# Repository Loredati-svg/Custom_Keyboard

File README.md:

# RP2040 Macropad – 9 Keys & 2 Rotary Encoders

A custom 9-key macropad with two rotary encoders and per-key RGB lighting, designed from scratch in **KiCad 10** around a bare **RP2040** microcontroller.

---
## Libraries

This project uses the shared KiCad libraries from L2-Hardware.

1. Clone the library repository **in the same parent folder as your project folders**, so that it sits next to them:

```bash
   git clone https://github.com/L2-Hardware/Kicad_Libs
```

   Expected folder structure:

```
   Kicad/
   ├── Kicad_Libs/
   ├── Project1/
   ├── Project2/
   └── etc...
```

2. Inside the project folder, run the `bring_libs.bat` script to import the libraries into the project.
---
## Features

- **9 mechanical keys** in a 3×3 grid (Cherry MX compatible, PCB-mount, standard 19.05 mm pitch)
- **2 rotary encoders** with push button (Bourns PEC12R, 12 detents) – e.g. volume, scrolling, media control
- **Per-key RGB lighting** with 9 addressable SK6812MINI-E LEDs (reverse-mount, shining through the switch)
- **USB-C** connector (USB 2.0 Full Speed)
- **Bare RP2040** design (no module): QSPI flash, crystal and power supply on board
- **4-layer PCB**, all SMD components on the bottom side, only switches and encoders on top
- Designed for **QMK / VIA** firmware

---

## Block Diagram

```
USB-C ──► Polyfuse ──► VBUS (5 V) ──┬──► AP2112K-3.3 ──► +3V3 ──► RP2040, Flash, pull-ups
  │                                 │
  │                                 └──► SN74LV1T34 (3.3 V → 5 V) ──► SK6812MINI-E ×9 (daisy chain)
  │
  └── D+/D− ──► USBLC6-2SC6 (ESD) ──► 27 Ω ──► RP2040 USB
                                               │
                         W25Q32 QSPI Flash ◄───┤
                         12 MHz Crystal    ◄───┤
                         9 Keys            ◄───┤ GPIO0–8
                         2 Encoders        ◄───┤ GPIO9–14
                         LED data          ◄───┘ GPIO15
```

---

## Hardware

| Block | Part | Notes |
|---|---|---|
| MCU | **RP2040** (QFN-56) | Dual Cortex-M0+, internal 1.1 V core regulator |
| Flash | **W25Q32JV** (4 MB, QSPI) | Stores the firmware |
| Clock | **ABM8-272-T3** 12 MHz | 15 pF load caps, 1 kΩ series resistor on XOUT (per RP2040 hardware design guide) |
| LDO | **AP2112K-3.3** | 600 mA, VBUS → 3.3 V |
| USB | USB-C 16-pin receptacle | 5.1 kΩ pull-downs on CC1/CC2 (device/UFP) |
| ESD | **USBLC6-2SC6** | Flow-through layout on D+/D− |
| Protection | Resettable polyfuse | On VBUS input |
| Keys | Cherry MX compatible switches | Direct GPIO connection, no matrix / no diodes |
| Encoders | **Bourns PEC12R-4120F-S0012** | 12 pulses / 12 detents, push switch |
| LEDs | **SK6812MINI-E** ×9 | Reverse-mount, powered from VBUS |
| Level shifter | **SN74LV1T34** | Translates the 3.3 V LED data line to 5 V |

---

## Design Notes

**Direct-wired keys.** With only 9 keys and 2 encoders the RP2040 has plenty of GPIOs, so every key is wired directly to its own GPIO with the internal pull-up enabled. No key matrix and no diodes are needed, and there is no ghosting by design.

**Encoder filtering.** Each encoder channel (A/B) uses a 10 kΩ external pull-up plus an RC low-pass filter (10 kΩ / 10 nF, τ ≈ 0.1 ms) to suppress contact bounce in hardware, while still allowing fast rotation.

**LED data level shifting.** The SK6812 LEDs are supplied from 5 V, so their minimum input-high threshold is ≈ 0.7 × VDD = 3.5 V, above the RP2040's 3.3 V output. A single-gate SN74LV1T34 buffer powered from VBUS shifts the data line to 5 V. A 33 Ω series resistor dampens ringing, and a 10 kΩ pull-down keeps the data line low while the MCU is booting, so the LEDs do not flash randomly at power-up.

**LED power.** Each LED has its own 100 nF decoupling capacitor, plus a 10 µF bulk capacitor on VBUS. LED brightness should be capped in firmware to stay within the 500 mA USB 2.0 budget.

**USB.** The RP2040 runs USB 2.0 Full Speed (12 Mbps). D+/D− are routed as a differential pair over an unbroken ground plane, with the ESD protection in flow-through configuration and the 27 Ω series resistors placed close to the MCU.

**Boot mode.** A BOOT push-button pulls QSPI_SS low through a 1 kΩ resistor. Holding it while plugging in USB starts the RP2040 USB mass-storage bootloader (`RPI-RP2`). No reset button is needed: unplugging and replugging the cable does the same job. SWD (SWCLK/SWDIO) is exposed on test points for debugging.

---

## PCB

- **4 layers**, 1.6 mm
  - `F.Cu` – key / encoder signals
  - `POWER` – power plane (+3V3 / VBUS), some low-speed routing
  - `GND` – solid ground plane, reference for USB and bottom-side signals
  - `B.Cu` – all SMD components, USB pair
- **Single-sided SMD assembly** (bottom) to reduce assembly cost. Switches and encoders are through-hole and hand-soldered on top.
- Board cut-outs under each switch for the reverse-mount LEDs
- 4× **M3 mounting holes** for standoffs / case

---

## Pinout

| Function | GPIO |
|---|---|
| Keys SW2–SW10 | GP0 – GP8 |
| Encoder VR2 – A / B / Push | GP9 / GP10 / GP11 |
| Encoder VR1 – A / B / Push | GP12 / GP13 / GP14 |
| RGB LED data (9 LEDs) | GP15 |
| SWD | SWCLK / SWDIO (test points) |

---

## Flashing

1. Hold the **BOOT** button.
2. Plug in the USB-C cable.
3. Release the button. A drive called `RPI-RP2` appears.
4. Drag and drop the `.uf2` firmware file onto it. The board reboots automatically.

After the first flash, the bootloader can also be entered from a key mapped to `QK_BOOT` in QMK.

---

## Firmware

Planned: **QMK** with **VIA/Vial** support
- Encoders mapped with `ENCODER_MAP` (e.g. volume up/down + mute, scroll, media keys)
- `RGB_MATRIX` with the WS2812 PIO driver on GP15

---

## Repository Structure

```
Custom-Keyboard/
├── Kicad_Project/   # KiCad schematic, PCB and project files
├── Lib/             # Custom symbols, footprints and 3D models
└── 3D/              # 3D models / renders
```

---

## Project Status

- [x] Schematic
- [x] PCB layout (4-layer)
- [x] DRC / ERC clean
- [ ] Manufacturing
- [ ] Bring-up and testing
- [ ] QMK firmware

---

## Author

**Lorenzo Dati** – Analog IC Designer

<!-- Choose a license, e.g. CERN-OHL-S-2.0 for hardware -->

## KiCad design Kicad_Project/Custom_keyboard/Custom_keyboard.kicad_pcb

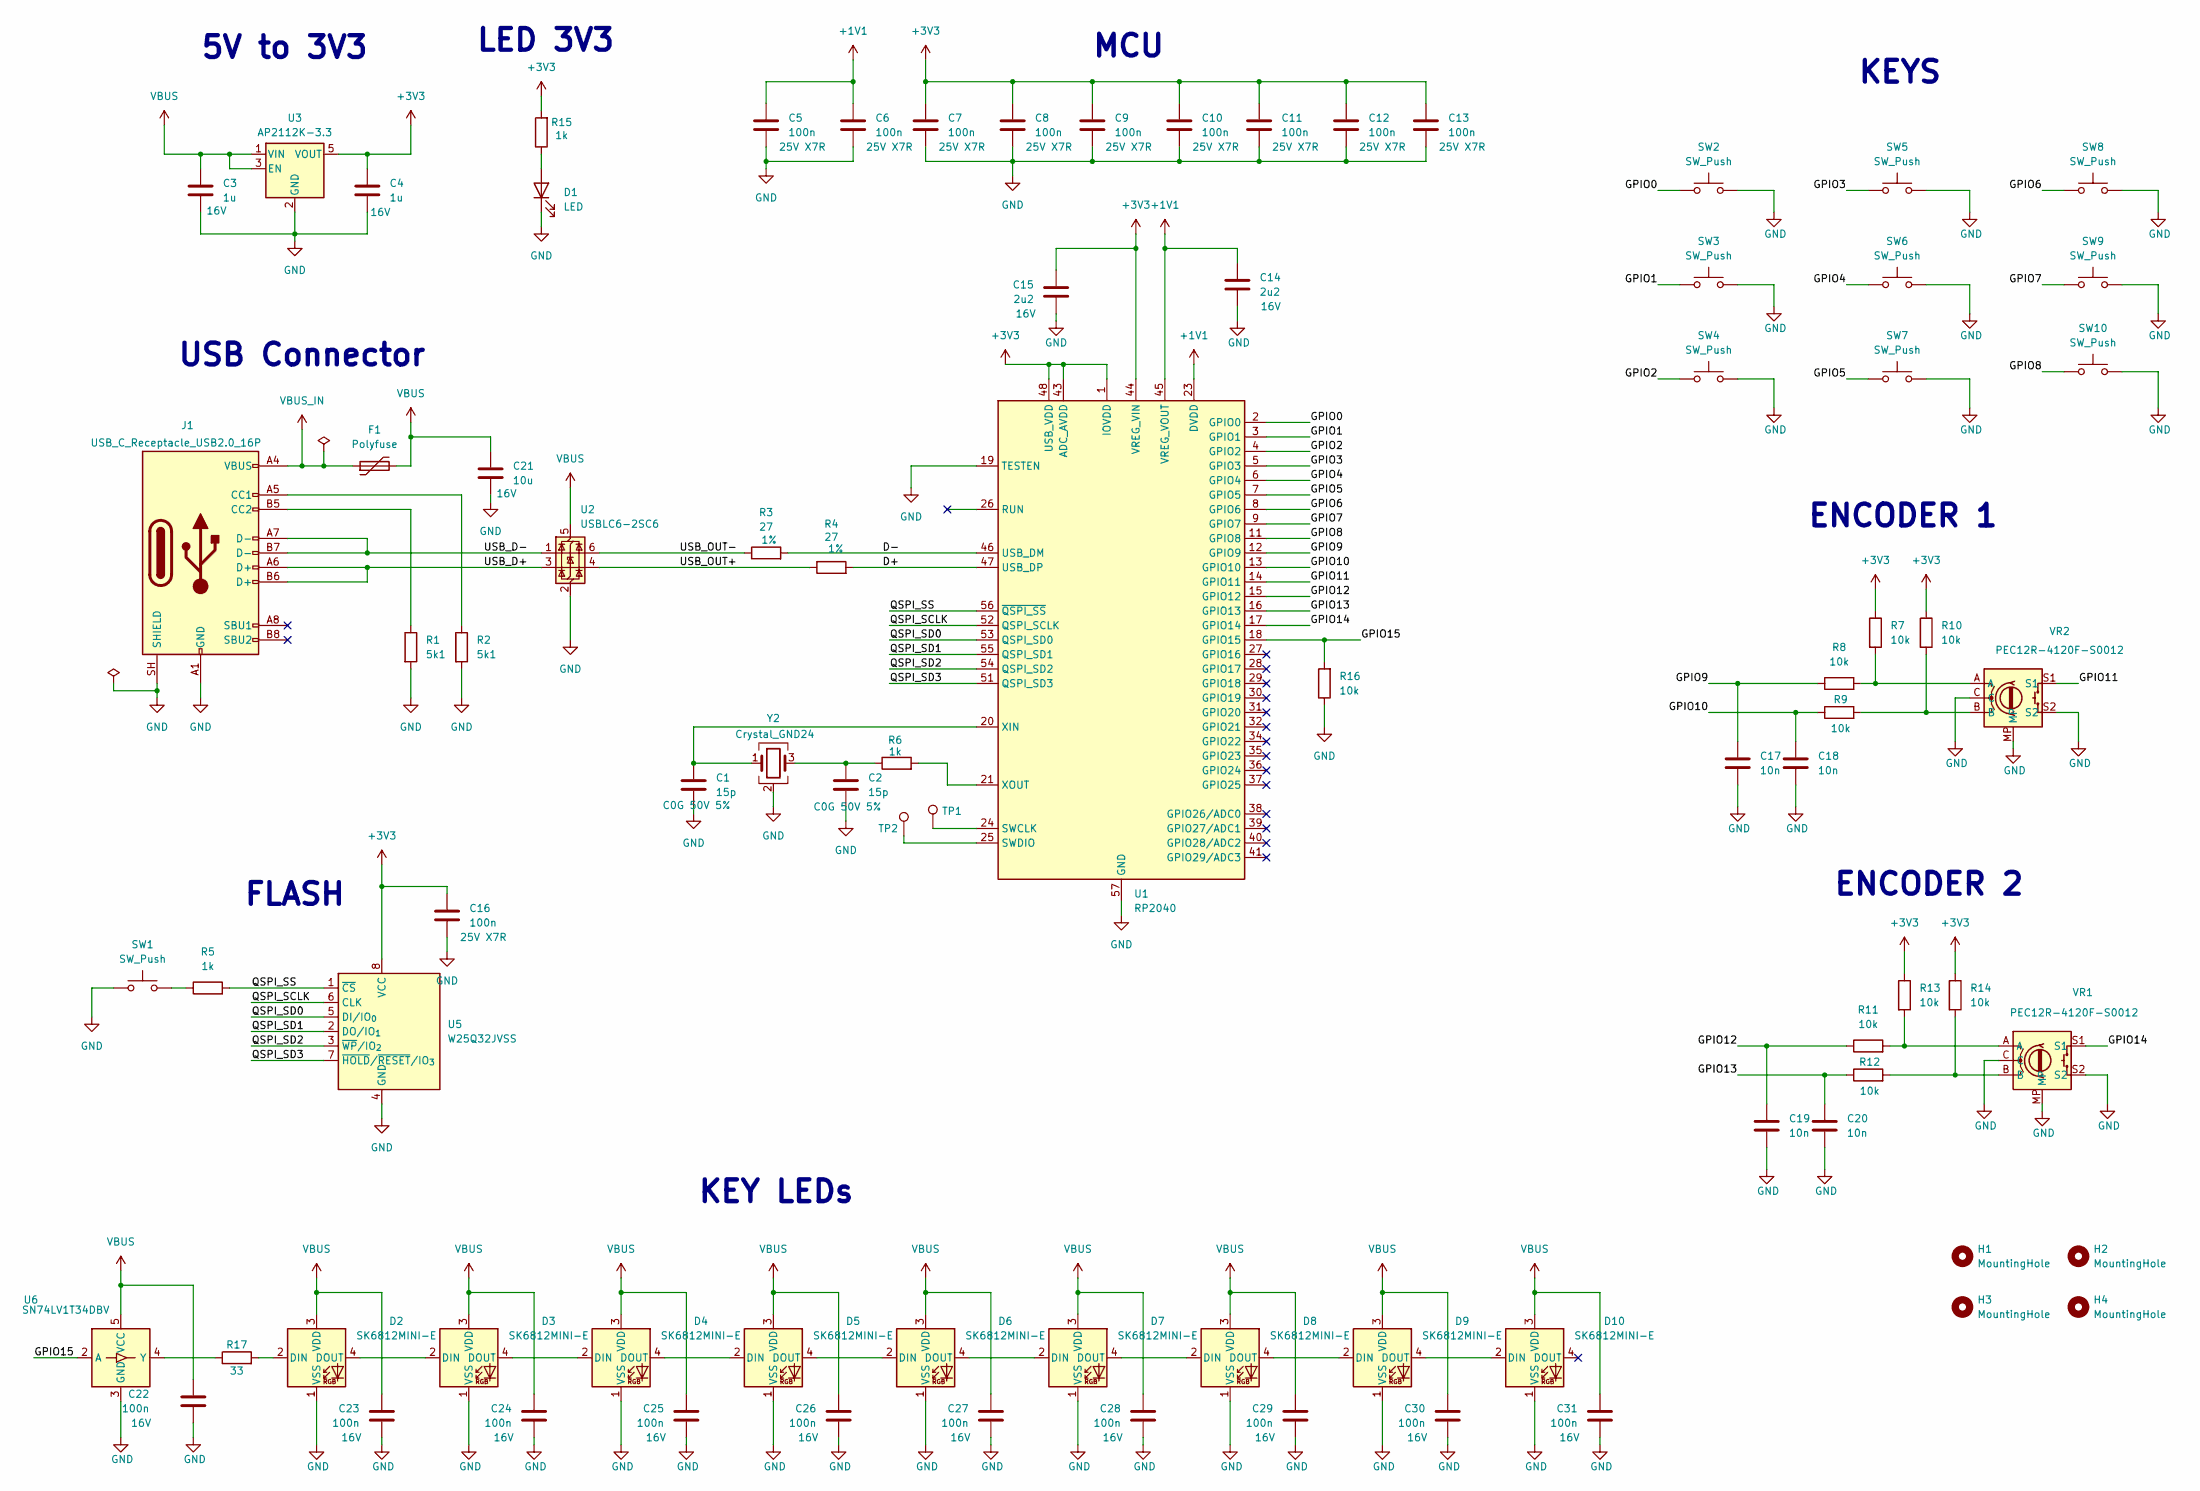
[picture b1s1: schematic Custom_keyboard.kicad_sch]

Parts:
C1, C2: 15p; C_0603_1608Metric; LCSC C20616249
C3, C4: 1u; C_0603_1608Metric; LCSC C5199872
C5, C6, C7, C8, C9, C10, C11, C12, C13, C16, C22, C23, C24, C25, C26, C27, C28, C29, C30, C31: 100n; C_0603_1608Metric; LCSC C1590
C14, C15: 2u2; C_0603_1608Metric; LCSC C43922
C17, C18, C19, C20: 10n; C_0603_1608Metric; LCSC C519406
C21: 10u; C_0603_1608Metric; LCSC C91606
D1: LED; LED_0805_2012Metric; LCSC C497951
D2, D3, D4, D5, D6, D7, D8, D9, D10: SK6812MINI-E; LED_SK6812MINI-E_3.2x2.8mm_P1.5mm_ReverseMount; LCSC C5149201
F1: Polyfuse; Fuse_1206_3216Metric; LCSC C371166
H1, H2, H3, H4: MountingHole; MountingHole_3.2mm_M3_ISO14580_Pad
J1: USB_C_Receptacle_USB2.0_16P; USB_C_Receptacle_GCT_USB4105-xx-A_16P_TopMnt_Horizontal; LCSC C3020560
R1, R2: 5k1; R_0603_1608Metric_Pad0.98x0.95mm_HandSolder; LCSC C2907044
R3, R4: 27; R_0603_1608Metric_Pad0.98x0.95mm_HandSolder; LCSC C2907136
R5, R6, R15: 1k; R_0603_1608Metric_Pad0.98x0.95mm_HandSolder; LCSC C2907002
R7, R8, R9, R10, R11, R12, R13, R14, R16: 10k; R_0603_1608Metric_Pad0.98x0.95mm_HandSolder; LCSC C2906982
R17: 33; R_0603_1608Metric_Pad0.98x0.95mm_HandSolder; LCSC C2909394
SW1: SW_Push; SW_SPST_PTS810; LCSC C116501
SW2, SW3, SW4, SW5, SW6, SW7, SW8, SW9, SW10: SW_Push; SW_Cherry_MX_1.00u_PCB; LCSC CPG151101D01
TP1: TestPoint_Pad_1.5x1.5mm
TP2: TestPoint; TestPoint_Pad_1.5x1.5mm
U1: RP2040; QFN-56-1EP_7x7mm_P0.4mm_EP3.2x3.2mm; LCSC C2040
U2: USBLC6-2SC6; SOT-23-6; LCSC C2827654
U3: AP2112K-3.3; SOT-23-5; LCSC C23380830
U5: W25Q32JVSS; SOIC-8_5.3x5.3mm_P1.27mm; LCSC C179173
U6: SN74LV1T34DBV; SOT-23-5; LCSC C100024
VR1, VR2: PEC12R-4120F-S0012; PEC12R4120FS0012; Manufacturer_Part_Number PEC12R-4120F-S0012; Mouser Part Number 652-PEC12R-4120F-S12
Y2: Crystal_GND24; Crystal_SMD_3225-4Pin_3.2x2.5mm; LCSC C20625731

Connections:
+1V1: C5.1, C6.1, C14.1, U1.23 (DVDD), U1.45 (VREG_VOUT), U1.50 (DVDD)
+3V3: C4.1, C7.1, C8.1, C9.1, C10.1, C11.1, C12.1, C13.1, C15.1, C16.1, R7.1, R10.1, R13.1, R14.1, R15.2, U1.1 (IOVDD), U1.10 (IOVDD), U1.22 (IOVDD), U1.33 (IOVDD), U1.42 (IOVDD), U1.43 (ADC_AVDD), U1.44 (VREG_VIN), U1.48 (USB_VDD), U1.49 (IOVDD), U3.5 (VOUT), U5.8 (VCC)
/D+: R4.2, U1.47 (USB_DP)
/D-: R3.2, U1.46 (USB_DM)
/GPIO0: SW2.1, U1.2 (GPIO0)
/GPIO1: SW3.1, U1.3 (GPIO1)
/GPIO2: SW4.1, U1.4 (GPIO2)
/GPIO3: SW5.1, U1.5 (GPIO3)
/GPIO4: SW6.1, U1.6 (GPIO4)
/GPIO5: SW7.1, U1.7 (GPIO5)
/GPIO6: SW8.1, U1.8 (GPIO6)
/GPIO7: SW9.1, U1.9 (GPIO7)
/GPIO8: SW10.1, U1.11 (GPIO8)
/GPIO9: C17.1, R8.1, U1.12 (GPIO9)
/GPIO10: C18.1, R9.1, U1.13 (GPIO10)
/GPIO11: U1.14 (GPIO11), VR2.S1
/GPIO12: C19.1, R11.1, U1.15 (GPIO12)
/GPIO13: C20.1, R12.1, U1.16 (GPIO13)
/GPIO14: U1.17 (GPIO14), VR1.S1
/GPIO15: R16.2, U1.18 (GPIO15), U6.2 (A)
/QSPI_SCLK: U1.52 (QSPI_SCLK), U5.6 (CLK)
/QSPI_SD0: U1.53 (QSPI_SD0), U5.5 (DI/IO_{0})
/QSPI_SD1: U1.55 (QSPI_SD1), U5.2 (DO/IO_{1})
/QSPI_SD2: U1.54 (QSPI_SD2), U5.3 (~WP/IO_{2})
/QSPI_SD3: U1.51 (QSPI_SD3), U5.7 (~HOLD/~RESET/IO_{3})
/QSPI_SS: R5.2, U1.56 (~QSPI_SS), U5.1 (~CS)
/USB_D+: J1.A6 (D+), J1.B6 (D+), U2.3 (I/O2)
/USB_D-: J1.A7 (D-), J1.B7 (D-), U2.1 (I/O1)
/USB_OUT+: R4.1, U2.4 (I/O2)
/USB_OUT-: R3.1, U2.6 (I/O1)
GND: C1.2, C2.2, C3.2, C4.2, C5.2, C6.2, C7.2, C8.2, C9.2, C10.2, C11.2, C12.2, C13.2, C14.2, C15.2, C16.2, C17.2, C18.2, C19.2, C20.2, C21.2, C22.2, C23.2, C24.2, C25.2, C26.2, C27.2, C28.2, C29.2, C30.2, C31.2, D1.1 (K), D2.1 (VSS), D3.1 (VSS), D4.1 (VSS), D5.1 (VSS), D6.1 (VSS), D7.1 (VSS), D8.1 (VSS), D9.1 (VSS), D10.1 (VSS), J1.A1 (GND), J1.A12 (GND), J1.B1 (GND), J1.B12 (GND), J1.SH (SHIELD), R1.2, R2.2, R16.1, SW1.1, SW2.2, SW3.2, SW4.2, SW5.2, SW6.2, SW7.2, SW8.2, SW9.2, SW10.2, U1.19 (TESTEN), U1.57 (GND), U2.2 (GND), U3.2 (GND), U5.4 (GND), U6.3 (GND), VR1.C, VR1.MP, VR1.S2, VR2.C, VR2.MP, VR2.S2, Y2.2 (G), Y2.4 (G)
unnamed: C2.1, R6.1, Y2.3
unnamed: D1.2 (A), R15.1
unnamed: D2.2 (DIN), R17.2
unnamed: D2.4 (DOUT), D3.2 (DIN)
unnamed: D3.4 (DOUT), D4.2 (DIN)
unnamed: D4.4 (DOUT), D5.2 (DIN)
unnamed: D5.4 (DOUT), D6.2 (DIN)
unnamed: D6.4 (DOUT), D7.2 (DIN)
unnamed: D7.4 (DOUT), D8.2 (DIN)
unnamed: D8.4 (DOUT), D9.2 (DIN)
unnamed: D9.4 (DOUT), D10.2 (DIN)
unnamed: J1.A5 (CC1), R2.1
unnamed: J1.B5 (CC2), R1.1
unnamed: R5.1, SW1.2
unnamed: R7.2, R8.2, VR2.A
unnamed: R9.2, R10.2, VR2.B
unnamed: R11.2, R13.2, VR1.A
unnamed: R12.2, R14.2, VR1.B
unnamed: TP1.1 (1_1), U1.24 (SWCLK)
unnamed: TP2.1 (1_1), U1.25 (SWDIO)
unnamed: C1.1, U1.20 (XIN), Y2.1
unnamed: R6.2, U1.21 (XOUT)
unnamed: R17.1, U6.4 (Y)
VBUS: C3.1, C21.1, C22.1, C23.1, C24.1, C25.1, C26.1, C27.1, C28.1, C29.1, C30.1, C31.1, D2.3 (VDD), D3.3 (VDD), D4.3 (VDD), D5.3 (VDD), D6.3 (VDD), D7.3 (VDD), D8.3 (VDD), D9.3 (VDD), D10.3 (VDD), F1.2, U2.5 (VBUS), U3.1 (VIN), U3.3 (EN), U6.5 (VCC)
VBUS_IN: F1.1, J1.A4 (VBUS), J1.A9 (VBUS), J1.B4 (VBUS), J1.B9 (VBUS)

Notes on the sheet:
LED 3V3
KEY LEDs
MCU
USB Connector
ENCODER 1
FLASH
5V to 3V3
KEYS
ENCODER 2

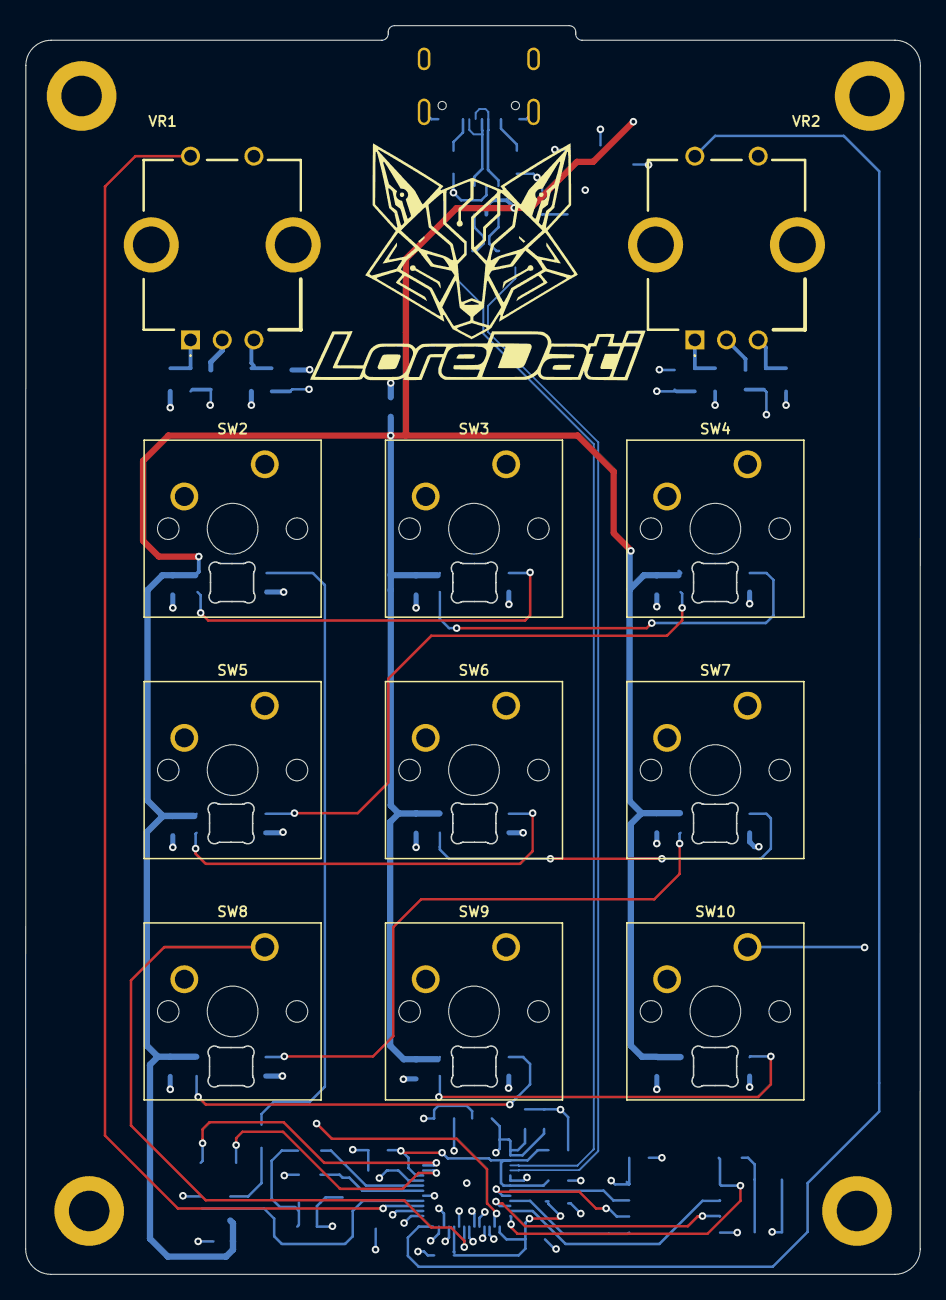
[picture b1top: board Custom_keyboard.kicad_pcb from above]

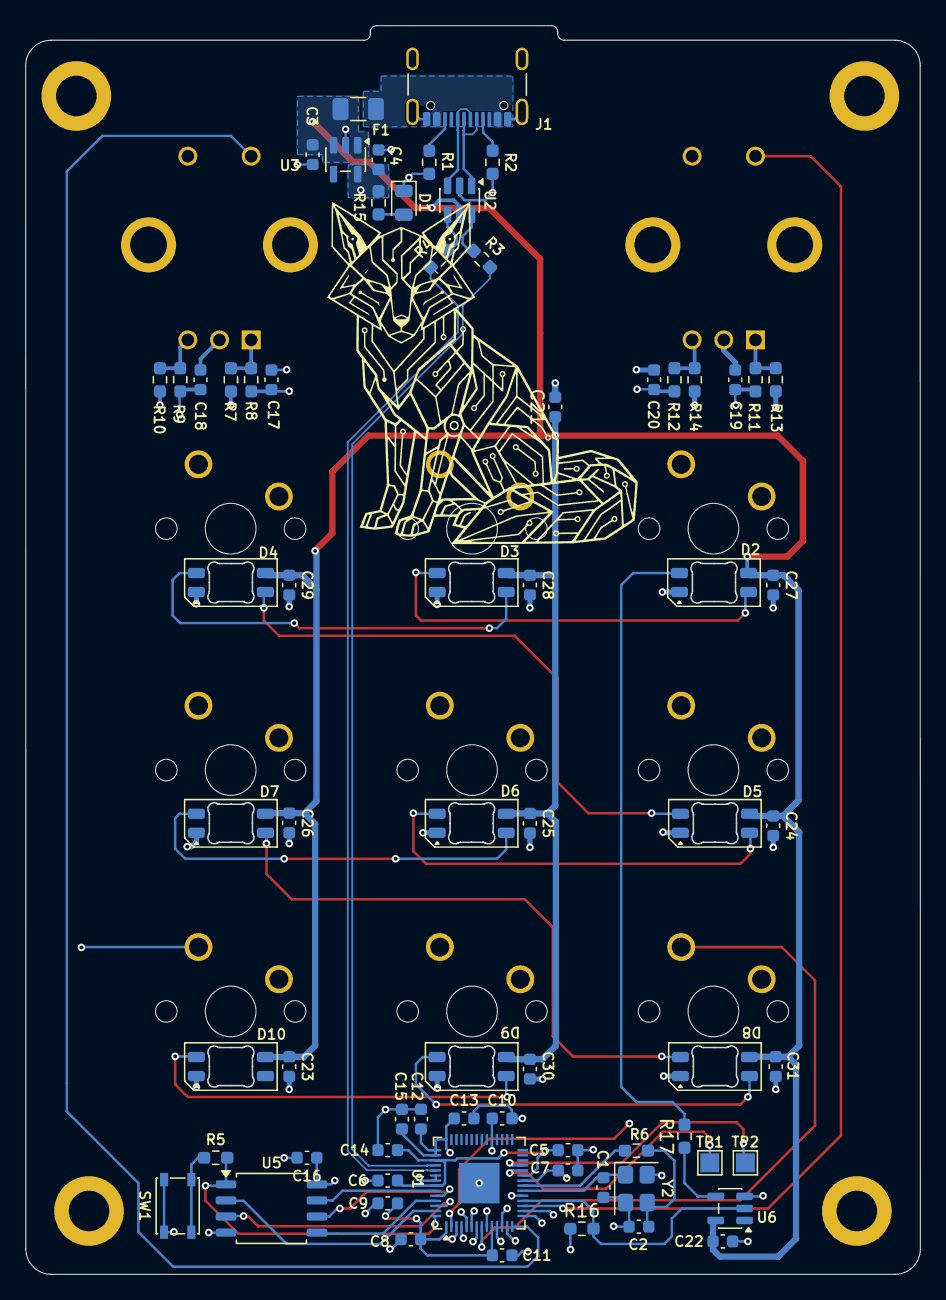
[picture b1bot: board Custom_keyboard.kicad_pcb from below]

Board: 4 copper layers, 70.6 x 98.5 mm, 84 parts (69 on the bottom side), 56 nets.

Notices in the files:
README.md:
License: CERN-OHL-P
